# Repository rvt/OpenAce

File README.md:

# GATAS Conspicuity Device

[📋 Changelog](./CHANGELOG.md) | [🎯 Wiki](https://rvt.github.io/gatas-doc/)

The GATAS Conspicuity device is designed for General Aviation pilots flying in areas where multiple
protocols, such as OGN, Flarm, ADS-L and FANET, are used. It can transmit and receive multiple
protocols simultaneously (excluding sending ADS-B) using one or more transceiver modules. All
received traffic is sent to your Electronic Flight Bag (EFB), such as SkyDemon, via the GDL90
protocol via WIFI or NMEA via bluetooth or WIFI.

The device is built around the Raspberry RP2040/RP2350 and can be configured with a custom PCB that
supports either two transceivers or a simpler configuration with one with modules from Waveshare
which makes it more of a plug-and-play. In both setups, it can send and receive all protocols using
time-sharing technology. The device can store configurations for multiple aircraft, which can be
selected through an easy-to-use web interface or via gatasServer

Powered by a Li-Ion battery, the device includes a PCB with a USB-C charger. The estimated battery
life is between 6 and 10 hours, though this is subject to further testing.

For FLARM it's current range has been t ested up to 24Km (see below screenshots) but on average a
good 15Km can be expected. This will give you plenty of time to avoid the traffic. EFBs like
SkyDemon can also send out audible traffic warnings.

Note: Although it's primary design is based around GA traffic, there is nothing in the hardware to
prevent other use cases like gliders, paragliders and hang gliders. The goal of the project is to be
seen by transmitting different protocols and be able to see them.

| <br>Additional traffic via gatasServer                                                       |  <br> soaring planes directly via FLARM                |
|--------------------------------------------------------------------------------------------------------------------------------------|---------------------------------------------------------------------------------------------|
|  Showing range of 24Km                                                                | <br> Two Tranceiver Version I have been flying with |
|  <br> GATAS Server selecting Aircraft                                                    |  <br> All modules                              |
|   <br> [GATAS Pulse Build Instructions](https://github.com/rvt/openace/wiki/gatas-Pulse) |  <br/> GATAS Pulse                                  |

> [!NOTE]
> The screenshot of SkyDemon was taken from the car while driving for safety reasons. The screenshot
> of the web interface showing the 24Km was taken while parked and the device placed on top of the
> car
> for better air-2-air visibility.

## ADS-L Issue 2 — Ground Station Mode & Traffic Uplink

**New in 2.0.0**: GATAS now supports **ADS-L Issue 2** including ground station mode and traffic uplink. In ground
station mode the device not only transmits its own position but also re-broadcasts received traffic
back into the ADS-L network as uplink frames, making nearby traffic visible to other ADS-L
participants that would otherwise be out of range. This includes any traffic received via Gatas Connect and thus showing additional MLAT traffic.
This is ideal if you have glider fields and want to inform nearby traffic that a fields is active.
A maximum of 10 aircraft closest to the groundstation will be relayed.

Base station mode is active and relaying additional traffic.

## Radio Protocol Support

Radio Protocol is the method used to communicate with other conspicuity devices

| Radio Protocol.        | Send               | Receive            | Multi Protocol     |
|------------------------|--------------------|--------------------|--------------------|
| OGN                    | :heavy_check_mark: | :heavy_check_mark: | :heavy_check_mark: |
| ADS-L                  | :heavy_check_mark: | :heavy_check_mark: | :heavy_check_mark: |
| FLARM (2024)           | :heavy_check_mark: | :heavy_check_mark: | :heavy_check_mark: |
| FANET                  | :heavy_check_mark: | :heavy_check_mark: | :heavy_check_mark: |
| ADS-B via gatasConnect | :no_entry:         | :heavy_check_mark: | :heavy_minus_sign: |
| PAW (2026 uses ADS-L)  | :heavy_check_mark: | :heavy_check_mark: | :heavy_check_mark: |

\* Multi Protocol is a feature of GATAS that allows to enable multiple protocols both send and
receive on a single transceiver by sharing the air time. The Transceiver will alternate between the
different protocols and prioritize a specific protocol when it receives data for that protocol.

**Adaptive Protocol Prioritisation (New in 2.0.0)**: GATAS now intelligently allocates more listening slots
for protocols that are actively receiving traffic, increasing pings per aircraft and improving overall situational awareness.

- Fanet support sending and receving including forwaring of FANET messages
- gatasConnect is a protocol and service to receive additional traffic information via mobile
  connection.

\* PAW legacy protocol is not supported, only their new ADS-L version

### Communication support

Communication support is what protocols are supported to other devices like electronic flight bags
or other equipment.

| Protocol     | Send UDP over WIFI | Receive UDP over WIFI | Send Bluetooth     | Send TCP over WIFI | Receiver over TCP WIFI |
|--------------|--------------------|-----------------------|--------------------|--------------------|------------------------|
| GDL90        | :heavy_check_mark: | N/A                   | N/A                | N/A                | N/A                    |
| AirConnect   | N/A                | N/A                   | :heavy_check_mark: | :heavy_check_mark: | N/A                    |
| Dump1090     | N/A                | N/A                   | N/A                | N/A                | :heavy_check_mark:     |
| gatasConnect | :heavy_check_mark: | :heavy_check_mark:    | N/A                | N/A                | :heavy_check_mark:     |

\* Sending GDL90 over Bluetooth is not used in the industry so this is currently not setup. If this
is really required, then this can be done. Do let me know the use case

### Tested with Electronic Flight Bag

GATAS is currently tested with SkyDemon only, If you made it work with any other software on Phone
or Tablet, do let me know so I can add or help out to make this work.

| EFB              | GDL90 over WIFI    | Bluetooth          | DataPort (NMEA) WIFI | Note                                                     |
|------------------|--------------------|--------------------|----------------------|----------------------------------------------------------|
| SkyDemon         | :heavy_check_mark: | :heavy_check_mark: | :heavy_check_mark:   | Tested Frequently during flight                          |
| EasyVFR 4        | :heavy_check_mark: |                    |                      |                                                          |
| ForeFlight       | :heavy_check_mark: |                    |                      | With part of ForeFLight extended spec and auto discovery |
| XTrack           |                    | :heavy_check_mark: |                      | Tested for connectivity                                  |
| Air navigation   | :heavy_check_mark: |                    |                      | Tested for connectivity                                  |
| SeeYou Navigator |                    | :heavy_check_mark: |                      | GPS and traffic targets shown                            |

> [!INFO]
> Thanks to  [PocketFMS / EasyVFR](https://easyvfr4.aero/nl/) for providing a Developer license of EasyVFR 4 to help test GATAS GDL90
>

## gatasConnect & gatasServer

**gatasConnect** and **gatasServer** provide a lightweight UDP-based protocol for receiving
additional traffic information.
This is still somewhat experimental but up an running and usable, it's free for you to use on the pre-configured server. Just enable
'gatasConnect' and ensure GATAS does have internet access via your mobile dev ice. Configure **Client** mode to connect to
your mobile's access point, how cool is that!

> [!TIP]
> gatasConnect uses [https://airplanes.live](https://airplanes.live) to to deliver internet-based traffic to your GATAS
> and into your EFB, including ADS-B Out and MLAT-derived traffic.
> If you have the chance, please consider adding airplanes.live to your existing feed or creating a new one.
> By doing so, you help improve traffic coverage for yourself and for others and contribute to safer flying.
>

## Features

- Online web application to select your configured aircraft
- Eliminates the need to manually connect to GATAS vi WIFI to choose an aircraft, saves time and
  you can focus on flying.
- Still compatible with GATAS aircraft selection via **gatas build in web service**
- Future support for **automatic aircraft selection** based on correlated ADS-B traffic

### Network Usage

- **Transmit:** ~52 bytes/second
- **Receive:** ~1024 bytes/second at 30 aircraft. (supports up to 30 nearby aircraft)

## External Libraries and frameworks used

Most libraries are used 'as-is' Some of them have been slightly modified for performance reasons,
compatibility or other reasons.

1. Raspberry PI PICO
   SDK [https://github.com/raspberrypi/pico-sdk](https://github.com/raspberrypi/pico-sdk)
2. FreeRTOS, GATAS uses tasks and timers and avoids loops and runs in multi-core SMP
   mode. [https://www.freertos.org](https://www.freertos.org)
3. LWiP Pretty cool and sometimes confusing TCP/IP protocol
   suite [https://savannah.nongnu.org/projects/lwip/](https://savannah.nongnu.org/projects/lwip/)
4. ArduinoJSON for loading and storing
   configuration [https://arduinojson.org](https://arduinojson.org)
5. etlcpp pretty awesome library written by John
   Wellbelove [https://www.etlcpp.com](https://www.etlcpp.com)
6. libcrc [https://github.com/lammertb/libcrc](https://github.com/lammertb/libcrc)
7. minmea for parsing NMEA
   sentences [https://github.com/kosma/minmea/](https://github.com/kosma/minmea/)
8. Catch2 for unit testing [https://github.com/catchorg/Catch2](https://github.com/catchorg/Catch2)
8. Easy to use FANET implementation in
   C++ [https://github.com/rvt/FANET](https://github.com/rvt/FANET)

# GATAS Disclaimer

> [!IMPORTANT] > **Important Notice: Use at Your Own Risk**
>
> The GATAS Conspicuity Device is provided "as is," without any guarantees or warranties of any
> kind. By using this device, you acknowledge and agree that:
>
> 1. **No Warranty**: The creators of GATAS make no claims or guarantees regarding the accuracy,
     reliability, or fitness for a specific purpose of the device or its associated software. This
     includes, but is not limited to, communication with OGN, Flarm, ADS-L, or any other protocols.
> 2. **Assumption of Risk**: You assume full responsibility for any and all risks associated with
     the use of GATAS. This includes, but is not limited to, risks related to hardware
     malfunctions, software issues, or incorrect transmission/interpretation of data.
> 3. **Limitation of Liability**: Under no circumstances shall the creators, contributors, or
     affiliates of GATAS be held liable for any direct, indirect, incidental, or consequential
     damages resulting from the use, misuse, or inability to use the device or its software.
> 4. **General Aviation Use**: GATAS is intended for use in General Aviation environments where
     multiple protocols such as OGN, Flarm, and ADS-L are used. It is **not certified** for
     professional or commercial aviation use and should not be relied upon as the sole source of
     traffic or navigation information.
> 5. **Compliance**: Users are responsible for ensuring that the use of GATAS complies with local
     aviation regulations and requirements. It is your responsibility to ensure that the device
     operates within the legal limits and safety standards for your jurisdiction.
> 6. **IFR Use**: GATAS is not intended for usage during an IFR flight.
>
> By using GATAS, you agree to the terms of this disclaimer and acknowledge that you are using the
> device and its software at your own risk.

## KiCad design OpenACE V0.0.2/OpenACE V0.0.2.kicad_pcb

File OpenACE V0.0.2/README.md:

# GATAS Conspicuity Device PCB

> **_NOTE:_**:
> This PCB design contains few, but not all changes from the V0.0.1 version (not published) and is still work in progress.

> **_NOTE:_**:
> Help wanted. If you have some PCB experence and also into flying, I would love to have some help with this!

Except for the memory card and the items fixed below, all items on this PCB has been verified to be working on the prototype board V0.0.1

To open and work on the PCB you need to install [KiCAD](https://www.kicad.org) KiCAD is an openSource schema and PCB design program which was used to design the PCB and to manufacture the PCB.

## Todo for V0.0.2

| Item                                                                                                       | Comment                                                                                                        | Status |
|------------------------------------------------------------------------------------------------------------|----------------------------------------------------------------------------------------------------------------|--------|
| S8050 has pin 1 and 2 rotated                                                                              |                                                                                                                | fixed  |
| LM3671 incorrectly has PIN 4 to GND                                                                        |                                                                                                                | fixed  |
| Flash Card is rotated                                                                                      | no comment...                                                                                                  | fixed  |
| Connection terminals too close                                                                             |                                                                                                                | fixed  |
| Remove breakout header                                                                                     | Safe space, not needed anyways...                                                                              |        |
| Use PICO 2350 (need to wait for WIFI version)                                                              | Faster CPU, floating point.                                                                                    |        |
| Add “Port” number on the PCB                                                                               | Might make people understand the board better                                                                  |        |
| Use MIC5219 instead of LM3671                                                                              | Price point, but need to validate                                                                              |        |
| Add silkscreen markers so pins are more clear                                                              |                                                                                                                |        |
| Add solder jumpers show what is the 5V side and 3.3V side                                                  |                                                                                                                |        |
| Put Positive and negative Battery connection to opposite end of the board                                  | to avoid longer connecte wires on the battery which can lead to shortcuts when assembling/working on the board |        |
| Battery charger is slightly too wide in length TP4056                                                      |                                                                                                                |        |
| Re-organize board: Pico in center facing ‘up’ with 868Mhz on left and right. GPS and ADSB under the 868Mhz | This will make the antenna more separate and make the board not so wide. Any other ideas?                      |        |
| Double switch as a PCB board item to have a battery charge, off and battery charge-on position             | Conserve battery, makes it easer to solder the board eg less wires and less chance of mistakes                 |        |
| Add + and - of battery connection to opposite of PCB instead of next to eachother                          | To ensure people create short wires on the battery to prevent shortcuts during testing/developing              |        |
| GPS chip should be able to be both internal and external                                                   |                                                                                                                |        |
| AHRS on the board?                                                                                         | people seem to want that..                                                                                     |        |

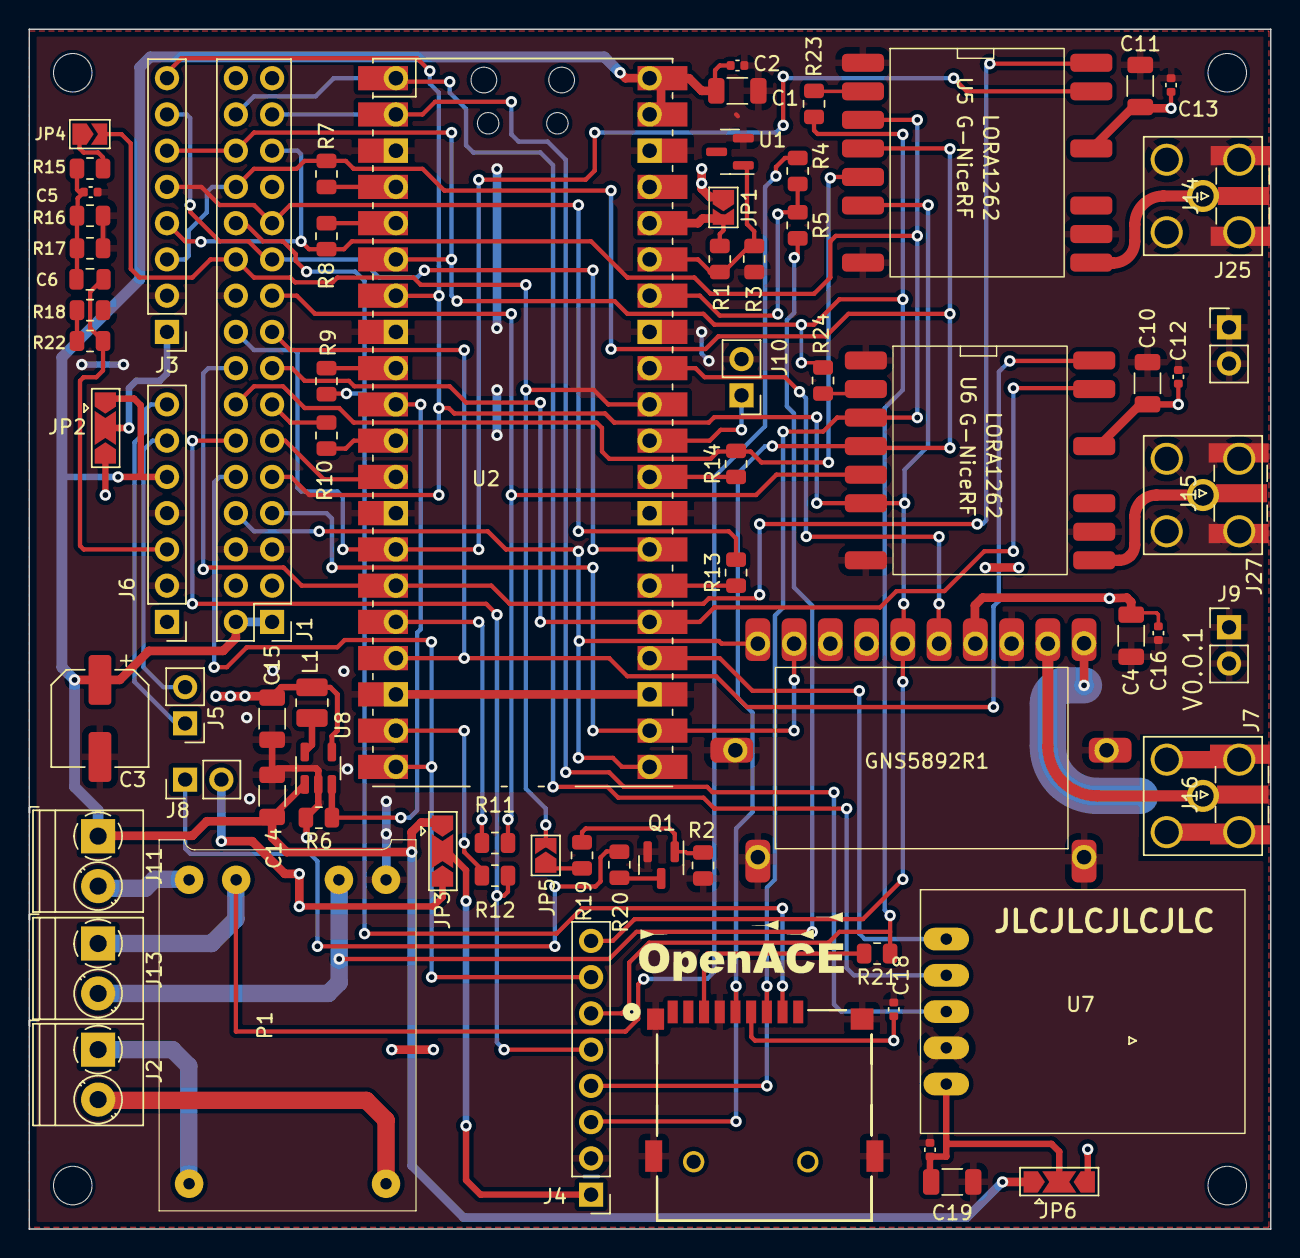
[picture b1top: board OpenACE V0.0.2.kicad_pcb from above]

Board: 2 copper layers, 87.0 x 84.1 mm, 79 parts (0 on the bottom side), 66 nets.

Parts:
C1, C4, C10, C11, C14, C15, C19: 10uF; C_1206_3216Metric
C2, C5, C12, C13, C16, C18, C20: 100nF; C_0402_1005Metric
C3: 220uF; CP_Elec_6.3x7.7
C6: 22uF; C_0805_2012Metric
GNS5892R1: GNS Module; GNS5892R1
H1, H2, H3, H4: MountingHole; MountingHole_2.7mm
J1: Conn_02x16_Odd_Even; PinHeader_2x16_P2.54mm_Vertical
J2: Power 5V; TerminalBlock_Phoenix_PT-1,5-2-3.5-H_1x02_P3.50mm_Horizontal
J3, J4: Conn_01x08_Pin; PinHeader_1x08_P2.54mm_Vertical
J5: Speaker; PinHeader_1x02_P2.54mm_Vertical
J6: Conn_01x07_Pin; PinHeader_1x07_P2.54mm_Vertical
J7, J25, J27: Conn_Coaxial; SMA_Amphenol_132203-12_Horizontal
J8, J9, J12: LED; PinHeader_1x02_P2.54mm_Vertical
J10: ~{RUN}; PinHeader_1x02_P2.54mm_Vertical
J11: Power Switch; TerminalBlock_Phoenix_PT-1,5-2-3.5-H_1x02_P3.50mm_Horizontal
J13: Battery; TerminalBlock_Phoenix_PT-1,5-2-3.5-H_1x02_P3.50mm_Horizontal
J14, J15, J16: Conn_Coaxial; SMA_Samtec_SMA-J-P-X-ST-EM1_EdgeMount
JP1: PICO Power; SolderJumper-2_P1.3mm_Open_TrianglePad1.0x1.5mm
JP2, JP3, JP6: SolderJumper_3_Open; SolderJumper-3_P2.0mm_Open_TrianglePad1.0x1.5mm
JP4: Speaker; SolderJumper-2_P1.3mm_Open_TrianglePad1.0x1.5mm
JP5: LED; SolderJumper-2_P1.3mm_Open_TrianglePad1.0x1.5mm
L1: 2.2uH; L_1008_2520Metric
P1: Power Module / Battery Charger; TP4056-charger-module
Q1: S8050; SOT-23
R1, R18: 750; R_0805_2012Metric
R2, R3, R6: 10K; R_0805_2012Metric
R4: 470K; R_0805_2012Metric
R5: 680K; R_0805_2012Metric
R7, R8, R9, R10, R11, R12, R13, R14, R21, R23, R24: 33; R_0805_2012Metric
R15, R16, R17, R20: 220; R_0805_2012Metric
R19, R22: 1K; R_0805_2012Metric
U1: LM4040DBZ-3; SOT-23
U2: SC0918; MODULE_SC0918
U5, U6: G-NiceRF / LORA1262; lora1262
U7: GPS Module M8N; gps_module_1
U8: LM3671MF-3.3; SOT-23-5
U9: MicroSD card (TF card); CONN9_0185-02_GSW

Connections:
+3V3: JP1.2 (B), R1.1, U2.36 (3V3_OUT)
+5V: C1.1, C2.1, C3.1, C14.1, J1.1, J1.2, J6.5, J11.1, JP2.1 (A), JP3.1 (A), JP6.1 (A), U2.39 (VSYS), U2.40 (VBUS), U8.1 (VIN)
/ADC_VRef: R1.2, R3.1, U1.1 (K), U2.35 (ADC_VREF)
/PWR+: J2.1, P1.5 (P+)
/PWR-: J2.2, P1.6 (P-)
/adsb_frame: GNS5892R1.5 (F_ind), U2.32 (GP27)
/bat+: J13.1, P1.1 (B+), R4.1
/bat-: J13.2, P1.2 (B-), R5.2
/battery_ref: R4.2, R5.1, U2.34 (GP28)
/gpio11_dio1: J1.18, U2.14 (GP10), U5.15 (DIO1)
/gpio12_busy1: J1.16, U2.15 (GP11), U5.16 (BUSY)
/gpio13_cs1: J1.14, R14.2, U5.5 (NSS)
/gpio21_cs3: J1.12, J4.5, R12.2
/gpio22_busy3: J1.10, J4.7, U2.20 (GP15)
/gpio31_tx4_cs2: J1.19, R11.1, U6.5 (NSS)
/gpio32_rx4_busy2: J1.17, U2.17 (GP13), U6.16 (BUSY)
/gpio33_pps_dio2: J1.15, U2.25 (GP19), U6.15 (DIO1)
/gpio41_tx5_cs4: J1.23, J3.5, R13.2
/gpio42_rx5_busy4: J1.21, J3.7, U2.27 (GP21)
/gpio51_tx3_cs5: J1.13, R10.1
/gpio52_rx3_busy5: J1.11, U2.12 (GP9)
/gpio61: J1.22, JP4.2 (B), JP5.2 (B), U2.31 (GP26)
/gpio71: R6.1, U2.10 (GP7), U8.3 (EN)
/gps_pps: U2.24 (GP18), U7.5 (PPS)
/mod_rst: GNS5892R1.6 (~Reset), J1.9, J3.8, J4.8, U2.7 (GP5), U5.6 (~RST), U6.6 (~RST)
/rx1: J1.29, U2.2 (GP1), U7.3 (TX)
/rx2: GNS5892R1.9 (Tx), J1.7, U2.22 (GP17)
/sdc_cs: J1.24, R9.1, U9.2 (DAT3/CD)
/spi_clk: J1.26, J3.3, J4.3, R7.1, U5.4 (SCK), U6.4 (SCK), U9.5 (CLK)
/spi_miso: J1.28, J3.6, J4.6, R21.1, R23.1, R24.1, U2.6 (GP4)
/spi_mosi: J1.27, J3.4, J4.4, R8.1, U5.3 (MOSI), U6.3 (MOSI), U9.3 (CMD)
/tx1: J1.30, U2.1 (GP0), U7.4 (RX)
/tx2: GNS5892R1.10 (Rx), J1.8, U2.21 (GP16)
GNDD: C1.2, C2.2, C3.2, C4.2, C5.2, C10.2, C11.2, C12.2, C13.2, C14.2, C15.2, C16.2, C18.2, C19.2, C20.2, GNS5892R1.3 (GND), GNS5892R1.11 (GND), GNS5892R1.12 (GND), GNS5892R1.13 (GND), GNS5892R1.14 (GND), J1.5, J1.6, J1.20, J3.2, J4.2, J6.2, J6.4, J9.1, J9.2, J10.2, J12.1, J12.2, J14.2 (Ext), J15.2 (Ext), J25.2 (Ext), J27.2 (Ext), P1.4 (-), Q1.2 (E), R2.1, R3.2, R6.2, R16.1, R17.1, R18.2, U1.2 (A), U2.3 (GND), U2.8 (GND), U2.13 (GND), U2.18 (GND), U2.23 (GND), U2.28 (GND), U2.33 (AGND), U2.38 (GND), U5.1 (GND), U5.8 (GND), U5.10 (GND), U6.1 (GND), U6.8 (GND), U6.10 (GND), U7.2 (GND), U8.2 (GND), U9.6 (VSS), U9.12 (SHIELD), U9.13 (SHIELD), U9.14 (SHIELD), U9.15 (SHIELD)
unnamed: C5.1, C6.1, R15.1, R16.2, R17.2
unnamed: GNS5892R1.1 (RF_Gnd), J7.2 (Ext), J16.2 (Ext)
unnamed: GNS5892R1.2 (RF_in), J7.1 (In), J16.1 (In)
unnamed: J3.1, JP2.2 (C)
unnamed: J4.1, JP3.2 (C)
unnamed: J5.1, J6.7
unnamed: J5.2, J6.6
unnamed: C6.2, J6.3, R22.2
unnamed: J8.1, R20.1
unnamed: J10.1, U2.30 (~RUN)
unnamed: J11.2, P1.3 (+)
unnamed: J14.1 (In), J25.1 (In), U5.9 (ANT)
unnamed: J15.1 (In), J27.1 (In), U6.9 (ANT)
unnamed: JP4.1 (A), R15.2
unnamed: JP5.1 (A), R19.1
unnamed: C19.1, C20.1, JP6.2 (C), U7.1 (VCC)
unnamed: Q1.1 (B), R2.2, R19.2
unnamed: Q1.3 (C), R20.2
unnamed: R18.1, R22.1
unnamed: R7.2, U2.4 (GP2)
unnamed: R8.2, U2.5 (GP3)
unnamed: R9.2, U2.9 (GP6)
unnamed: R10.2, U2.11 (GP8)
unnamed: R11.2, U2.16 (GP12)
unnamed: R12.1, U2.19 (GP14)
unnamed: R13.1, U2.26 (GP20)
unnamed: R14.1, U2.29 (GP22)
unnamed: R23.2, U5.2 (MISO)
unnamed: R24.2, U6.2 (MISO)
unnamed: L1.1, U8.5 (SW)
unnamed: R21.2, U9.7 (DAT0)
VCC: C4.1, C10.1, C11.1, C12.1, C13.1, C15.1, C16.1, C18.1, GNS5892R1.4 (VDD), J1.3, J1.4, J8.2, JP1.1 (A), JP2.3 (B), JP3.3 (B), JP6.3 (B), L1.2, U5.13 (VCC), U6.13 (VCC), U8.4 (FB), U9.4 (VDD)

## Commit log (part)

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2024-12-30 Update Dockerfile for latest SDK
2024-12-30 Remove duplicate code bluetooth.cpp
2024-12-30 try pip
2025-01-04 Updated pico_sdk_import.make
2025-01-04 Update bluetooth due to pairing issues. Moved flash store to a different location due to bluetooth bonding location. Updated UI so a user can set the vluetooth device name
2025-01-05 Patch github action env
2025-01-05 Two tasks for Idle and loading of all modules
2025-01-06 Re-Added __scratch_y data arrays Added RFCOMM / SPP for bluetooth Added CYW43_ to prevent Stack Overflows? Still not sure
2025-01-07 Allow to enable/Disable rfComm by setting, default disabled.
2025-01-19 Better baudrate detection on ublox Cleanup of uart_rx_f.h Fix bluetooth configuration and removed deprecated functions
2025-01-19 Added utils tests
2025-01-24 stack smash
2025-01-25 don't panic if module not found Renamed GpsTimeMsg to UtcTimeMsg to avoid confusion on what time reference it is. Handle potentional NAN from NMEA
2025-01-25 Fix aircraft tracker that deleted aircraft to quickly
2025-01-26 Code cleanup
2025-02-01 Prepare for different GPS devices Cleanup FreeRTOS tasks Removed a few unneeded filters in gpsdecoder Add statistics in dataport
2025-02-01 Wrap vDiagnosticsTask in configGENERATE_RUN_TIME_STATS
2025-02-07 Add configuration for Waveshare Lite Hardware Don't attempt to load HW whe not supported Hardware pins are now directly loaded from the hw module Added support for Waveshare L76B GPS module Added sup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
2025-02-11 Design for the TopGNSS GPS Antenna
2025-02-12 Design for the TopGNSS GPS Antenna Force handling queue when RMC is received
2025-02-24 FANET Tests
2025-03-02 Missing SPI numbering for 'pin' map
2025-03-03 Work FANET
2025-03-05 Increase BlueTooth queue to prevent that the queue runs full.
2025-03-06 Work FANET protocol
2025-03-30 Updated submodule references
2025-03-30 Integration of FANET with Initial branch
2025-03-30 Fix merge issue
2025-04-03 Cleanup ADSB
2025-04-03 Antenna Pattern for the 4 protocols
2025-04-03 Add FANET
2025-04-03 Incorrect change of size in addresscache.hpp
2025-04-04 Work bluetooth
2025-04-04 Removed Catch2
2025-04-04 Fix version ETLCPP cleanup bluetooth.cpp
2025-04-06 Change due to delegate changes in etlCPP Introduced a few 'raw' functions that are slightly faster then the non raw counterparts.
2025-04-06 Fix generated default config
2025-04-08 Upgrade FreeRTOS and SDK
2025-04-11 Groundspeed was still at knt instead of m/s
2025-05-02 Added capability for a Android/iOS Companion application to receive ADSB Data Small fix on the aircraft tracker Cleanup bluetooth handling.
2025-05-02 Fix build
2025-05-09 Changes startup sequence for faster startup and reconnect Fix issue on circularbuffer Removed Timer on the aircrafttracker
2025-05-13 Re-looked into altitudes and how each protocol handles it. With the modifications all altitudes are reported the same when using OGN base station
2025-05-26 Added initial design of the OpenAce Pulse Version
2025-05-26 Work on altitudes, rename variables and clarivication
2025-05-29 Add RP2350 compile option
2025-05-29 Add RP2350 compile option (#2)
2025-06-08 Update STL's / SCAD for build instructions wiki
2025-06-17 Rename OpenAce to new name of GA/TAS
2025-06-20 Bugfix single tranceiver
2025-06-28 US a specific DataFrame queue to receive packets to offload the transceiver Small UI changes Code cleanup on how to set the protocols order Removed tasks from 3 protocols because the FrameQueue can b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
2025-07-06 FLARM as a seperate module
2025-07-11 Removed FLARM in favour of submodule
2025-07-11 Add Channel hoping for other zones
2025-07-14 Added additional tests for Config module Added IdleMsg, Every5SecMsg, Every15SecMsg, Every30SecMsg so modules don't have to keep track of their own method to do something every once a while Prepare B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
2025-07-30 Changed COB's message format in preparation of gatasServer
2025-08-08 Fix: Correct various spelling and grammar errors
    This commit addresses multiple spelling and grammatical mistakes found in the project's documentation, user interface, and source code comments.
    The corrections improve the overall readability and professionalism of the codebase.
    Changes were made in the following files:
    - README.md
    - doc/heights.md
    - src/lib/flarmgatas/doc/nmi71bTG.md
2025-08-08 Prepare for gatasConnect
2025-08-20 Work GA/TAS Connect
2025-08-31 Working version GA/TAS Connect - gatasServer will be uploaded soon after cleanup of code Renaming of variables for clarification Ensure specific messages have long mutex timeouts because they are imp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
2025-09-05 Compatibility with Foreflight in Client Mode. Allow to see your local GA/TAS IP address from GA/TAS server
2025-09-13 RAII version of lwip lock Additional statistics for gatasConnect
2025-09-13 GA/TAS Connect Connectivity (#4)
    Add badge
    Working version GA/TAS Connect - gatasServer will be uploaded soon after cleanup of code
    Renaming of variables for clarification
    Ensure specific messages have long mutex timeouts because they are important
    Added gatasId needed for gatasServer to re-Configure devices
    Allow to see your local GA/TAS IP address from GA/TAS server
2025-09-15 Update default gatasCOnnect server IP
2025-10-01 Wrong place transmission counter
2025-10-01 Fix GLD90 when GATAS connects to a phone running an EFB
2025-10-02 Align WIFI password rules with firmware to 20 chars Always enable Bluetooth
2025-10-11 Removed CircularBuffer Removed StreamBuffer
    Created TCPCLient wrapper around LWiP
    Created Gulp class to help with reading streamed packages
    Created PacketByffer to help with writing packages
    Created DelimiterBitmap to help with splitting of packages
    Modified SemaphoreGuard to not take time as a template parameter
    ADSBDecoder: Reduce cache sizes
2025-10-12 Update all subrepos to their latest upstream changes
2025-10-12 Various (#5)
    * Wrong place transmission counter
    * Better respond to interface changes
    Only init mDNS once
    * Fix GLD90 when GATAS connects to a phone running an EFB
    * Align WIFI password rules with firmware to 20 chars
    Always enable Bluetooth
2025-10-20 gatasconnect over TCP Added spinlocking guard Auto Reconnect for TcpCLient
2025-10-21 Add missing lwippools.h
2025-10-21 Gatas connect tcp (#6)
    * gatasconnect over TCP
    * Added spinlocking guard
    * Auto Reconnect for TcpCLient
    * Improved logging
2025-10-26 Removed 'stop' virtuals. Reboot is fast enough (#7)
    Further tuned LWiP Stack
    Make use of __scratch_y on the PICO
    Changed data copy to use a spinlock rather than a mutex fort critical structures
2025-10-26 Re-Designed gatasconnect-udp to see if this one want's to go therough the Android Hotspot
2025-10-29 Fix Discord Invite
2025-10-31 try to convince cmake to that it depends on the gatas_gatt header iin bluetooth
2025-11-01 Change WIFI such that once it's in Client mode, it stays in Client mode by keep trying to connect to any configured AP's.
2025-11-07 Correctly de-initialise on WIFI change Show small aircraft instead of UNKNOWN to avoid UNKNOWN aircraft to be shown in the EFB. Might need a bit of extra research to further avoid this. It seems to b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
2025-11-12 Include Satellites in View for GPS
2025-11-20 Add option to measure PPS lag to RMC (developer only) Add option for L76B and Ublock to enable Software PPS, but preferred is hardware for much more accuracy Increase SSD/Wifi password to 32Byte Prov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
2025-11-22 Refactor: Use brace initialization for objects
    This commit refactors the codebase to use brace initialization {} instead of parenthesis () for object construction. This change improves code consistency and helps prevent vexing parse issues.
    The following files were modified:
    - src/lib/adsl/ace/adsl.hpp
    - src/lib/ogn/ace/ogn1.hpp
    - src/lib/gatasconnect/ace/gatasconnectudp.hpp
    - src/lib/gatasconnect/ace/tcp/gatasconnecttcp.hpp
2025-11-23 Fix a issue where POST requests from a Chrome type browser results in multiple pbuffers.
2025-11-24 GDL90 now does auto discovery for ForeFlight (to be tested, but looks good) Updated stl for Pulse version such that people don't have to split it anymore Better GATAS_LOG that logs FILE and LINE numb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
2025-11-27 For GDL90 Callsign handle it as SW Mod D For GDL90 handle uere based on 3D or DGPS For GDL90 force 'airborn' to avoid ForeFLight hiding aircraft GpsDecoder send a proper GpsFix with enum about 3D vs 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
2025-11-28 Add DDB so aircraft can be identified with NMEA or GDL90
2025-11-30 Added FLARM DDB https://www.flarmnet.org/files/ddb.csv Fix for iPhone 7 that didn't load the webside
2025-12-03 release builds
2025-12-04 Use array view functions that have fixed sizes
2025-12-06 Dump version number L76B in Debug Mode Fix: When WIFI Service does nto have any configured clients, but AP mode only set, ensure we still start a AP
2025-12-09 Removed option to disable the Access Point. If enabled, and Wifi is incorrectly configured then no connection is possible anymore and person needs to nuke.
2025-12-12 Added a flash_nuke_RP2350.uf2 so if people really get stuck, they can start over
2025-12-13 Allow to pu GATAS in AP mode from the UI Set the Airplane page as the default page and added the Actions Buttons in that page Updated DDB
2025-12-19 Fix GDL90 where when GPS had a fix it did not send the FF messages
2025-12-23 Reduce the number of spinlocks and use a global shared spinlock for copy of data only.
2026-01-01 works on new preambles
2026-01-06 Update WIKI link
2026-01-08 Handle preambles such that they are better compatible with other transceiver, mainly classic flarm
2026-01-09 Added hearybeat for HiltonSoftware - Need to find out what it is..
2026-02-28 ADSL Issue 2 implementation Added more tests
2026-02-28 Updated tests
2026-03-03 Fix FLARM sending and receiving
2026-03-03 Fix RP2350 builder server FreeRTOS Patch
2026-03-04 Fix release
2026-03-11 tidy up configuration pages
2026-03-22 Groundstation mode
2026-03-23 Fix regression FANET
2026-03-25 Update GATAS naming
2026-03-28 Fixed device error SX1262
2026-03-29 Updated TX Timing and visualisations
2026-04-02 Guards around a few containers
2026-04-05 Use xTaskNotifyWait instead of ulTaskNotifyTake
2026-04-08 Allow per protocol TX, RX or RX/TX
2026-04-09 Code Cleanup, fix random time issue.
2026-04-12 Prepare 2.0.0 release
2026-04-13 Update doc
2026-04-20 Prefere RADIO data over ADSB data when aircraft came in over multiple datasources.
2026-04-27 Fix antenna pattern to be relative to aircraft
2026-04-27 Update ADSL function in preparation for merging some codes later
2026-04-28 Track in FLARM if CRC corrections where performed
2026-04-30 - Better rendering of RadioTUnerTX and Protocol Timing in the UI - Moved the 'action' buttons to a seperate page in the UI
2026-05-02 Optimise cmake build
2026-05-02 Include cleanup
2026-05-15 Added GDL90 over bluetooth encoded in COBS
2026-05-16 Cleanup binarymessages.hpp
2026-05-17 Bluetooth advertising now splits the local name between the primary advertisement and scan response payloads, improving visibility of longer device names while keeping the custom service UUID adverti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
2026-05-19 Work on optimising BlueTooth
2026-05-20 Optimise sx1262 HAL for RTOS
2026-05-21 BaseModule: Optimise sx1262 HAL for RTOS BlueTooth: Ensure to always set txDirty
2026-05-23 Update tracker
2026-05-27 Aircraft Tracker Code Cleanup
2026-06-01 Allow change between AP or CLIENT from the mobile application.
2026-06-02 Bluetooth Cleanup
2026-06-11 Prepare release
2026-06-11 fix merge conflicts
2026-06-12 Added support for two named AceSPI instances
2026-06-13 Cleanup pins
2026-06-13 fix docker builds
2026-06-15 Work on predictor
